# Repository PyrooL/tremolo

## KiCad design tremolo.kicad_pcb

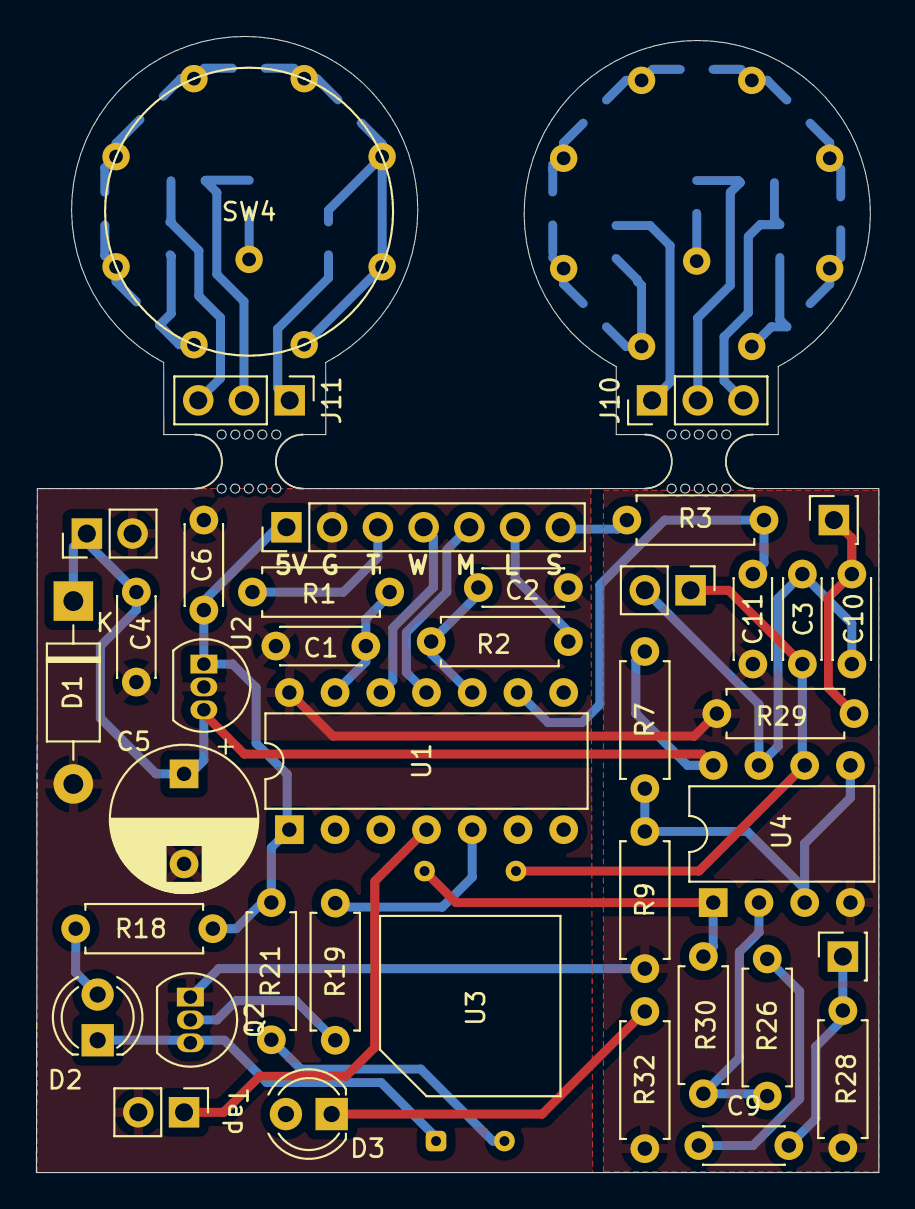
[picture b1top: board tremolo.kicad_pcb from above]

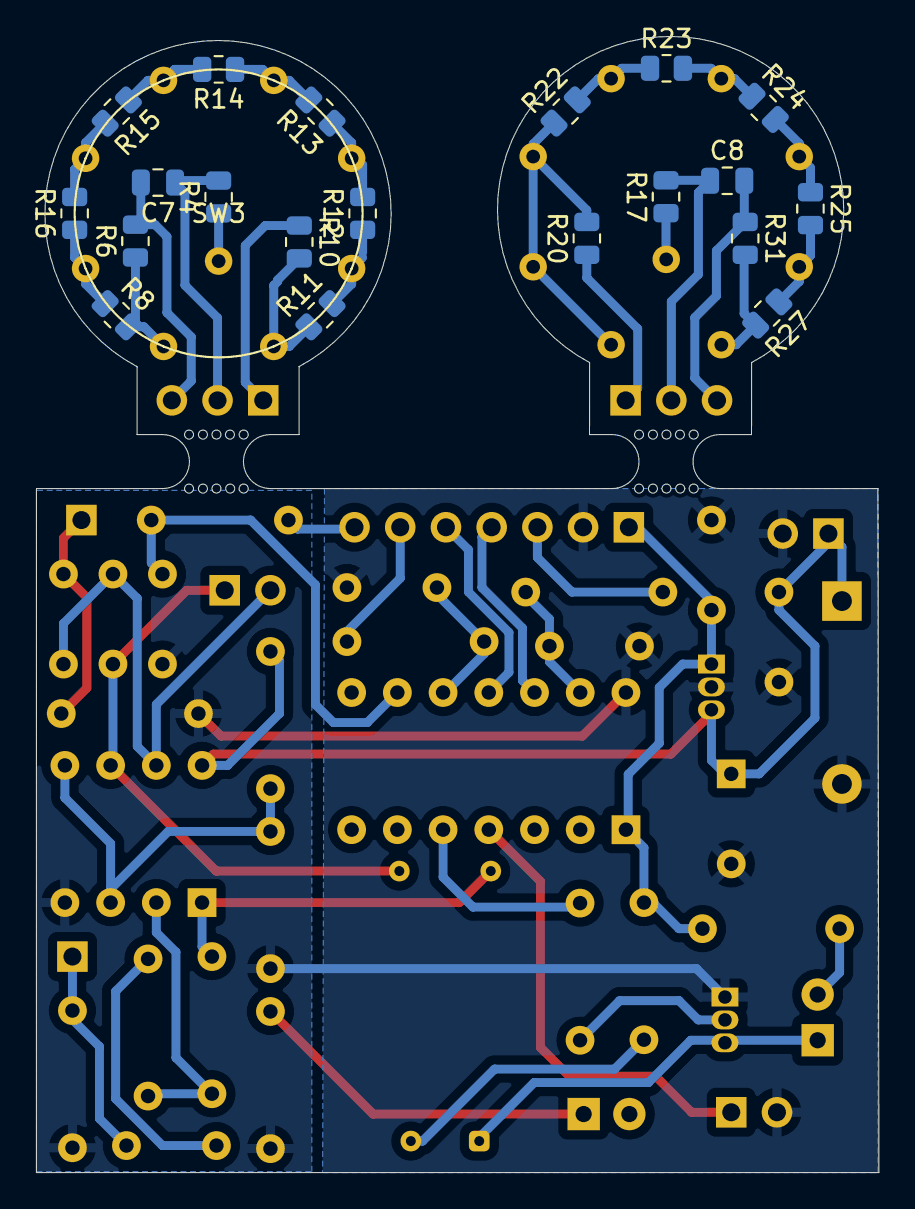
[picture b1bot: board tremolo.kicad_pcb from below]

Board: 2 copper layers, 46.8 x 63.1 mm, 62 parts (21 on the bottom side), 48 nets.

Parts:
C1, C2, C3, C4, C6: 100n; C_Disc_D4.3mm_W1.9mm_P5.00mm
C5: 470u; CP_Radial_D8.0mm_P5.00mm
C7, C8: 100n; C_0805_2012Metric
C9, C10: 1u; C_Disc_D4.3mm_W1.9mm_P5.00mm
C11: 22p; C_Disc_D4.3mm_W1.9mm_P5.00mm
D1: 1N4001; D_DO-41_SOD81_P10.16mm_Horizontal
D2: LFO_VIS; LED_D4.0mm
D3: ACTIVE; LED_D4.0mm
J1: Jack-DC; PinHeader_1x02_P2.54mm_Vertical
J4, J5: Conn_01x01_Female; PinSocket_1x01_P2.54mm_Vertical
J6: Conn_01x07; PinHeader_1x07_P2.54mm_Vertical
J10, J11: Conn_01x03; PinHeader_1x03_P2.54mm_Vertical
Q2: 2N3904; TO-92_Inline
R1, R2, R3: 1k; R_Axial_DIN0207_L6.3mm_D2.5mm_P7.62mm_Horizontal
R4, R17: 1k; R_0805_2012Metric
R6, R10, R31: 4.7k; R_0805_2012Metric
R7, R9: 100k; R_Axial_DIN0207_L6.3mm_D2.5mm_P7.62mm_Horizontal
R8, R11, R12, R13, R14, R15, R16, R22, R23, R24, R25, R27: 10k; R_0805_2012Metric
R18, R21, R32: 180; R_Axial_DIN0207_L6.3mm_D2.5mm_P7.62mm_Horizontal
R19: 10k; R_Axial_DIN0207_L6.3mm_D2.5mm_P7.62mm_Horizontal
R20: 25k; R_0805_2012Metric
R26, R30: 220k; R_Axial_DIN0207_L6.3mm_D2.5mm_P7.62mm_Horizontal
R28, R29: 1M; R_Axial_DIN0207_L6.3mm_D2.5mm_P7.62mm_Horizontal
RV4: 100k A; PinHeader_1x02_P2.54mm_Vertical
SW1: SW_Push; PinHeader_1x02_P2.54mm_Vertical
SW3, SW4: SW_Rotary8; RotaryEncoder_Adafruit_Mini_8
U1: TAPLFO3; DIP-14_W7.62mm
U2: L78L05_SOT89; TO-92L_Inline
U3: VTL5C; PerkinElmer_VTL5C
U4: TL072; DIP-8_W7.62mm
mouse-bite-3mm-slot, mouse-bite-3mm-slot#2: VAL**; mouse-bite-3mm-slot

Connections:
+5V: C6.1, J6.1, R18.1, R21.1, U1.1 (+5V), U2.1 (OUT)
+9V: C4.1, C5.1, D1.1 (K), J1.1, R7.1, U2.3 (IN), U4.8 (V+)
/+4V5: R7.2, R9.1, U4.3 (+), U4.5 (+)
/distort: C3.1, R3.2, U1.9 (DISTORT_CV)
/distort_RC: J6.7, R3.1
/level: C2.1, R2.2, U1.10 (LEVEL_CV)
/level_RC: J6.6, R2.1
/lfo_pwm: R19.2, U1.5 (PWM_OUT)
/multiplier: J6.5, U1.11 (MULTIPLIER_CV)
/multiplier/+5V: J11.1, R20.1
/multiplier/GND: C8.2, J11.3, R31.1
/multiplier/multiplier: C8.1, J11.2, R17.2
/sig_in: C9.2, J4.1, R28.1
/sig_out: C10.1, J5.1, R29.1
/tap_in: SW1.1, U1.4 (TAP_TEMPO)
/tempo: C1.1, R1.2, U1.13 (TEMPO_CV)
/tempo_RC: J6.3, R1.1
/waveform: J6.4, U1.12 (WAVEFORM_CV)
/waveform/+5V: J10.1, R10.1
/waveform/GND: C7.2, J10.3, R6.2
/waveform/waveform: C7.1, J10.2, R4.2
GND: C1.2, C2.2, C3.2, C4.2, C5.2, C6.2, D1.2 (A), J1.2, J6.2, Q2.1 (E), R9.2, R28.2, R29.2, R32.2, SW1.2, U1.14 (0V), U2.2 (GND), U4.4 (V-)
unnamed: C9.1, R26.2
unnamed: C10.2, C11.2, RV4.2, U4.7
unnamed: D2.2 (A), R18.2
unnamed: D2.1 (K), Q2.3 (C), U3.1 (-)
unnamed: D3.1 (K), R32.1
unnamed: Q2.2 (B), R19.1
unnamed: R4.1, SW3.9
unnamed: R6.1, R8.2, SW3.8
unnamed: R10.2, R11.1, SW3.1
unnamed: R11.2, R12.1, SW3.2
unnamed: R12.2, R13.1, SW3.3
unnamed: R13.2, R14.1, SW3.4
unnamed: R14.2, R15.1, SW3.5
unnamed: R15.2, R16.2, SW3.6
unnamed: R8.1, R16.1, SW3.7
unnamed: R17.1, SW4.9
unnamed: R20.2, R22.1, SW4.1, SW4.2, SW4.3
unnamed: R22.2, R23.1, SW4.4
unnamed: R23.2, R24.1, SW4.5
unnamed: R24.2, R25.1, SW4.6
unnamed: R25.2, R27.1, SW4.7
unnamed: R27.2, R31.2, SW4.8
unnamed: R30.1, U3.3, U4.1
unnamed: R21.2, U3.2 (+)
unnamed: R26.1, R30.2, U4.2 (-)
unnamed: C11.1, RV4.1, U3.4, U4.6 (-)

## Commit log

2023-12-23 cleanup
2023-12-23 Separate IO from main board
2023-12-23 THT version
